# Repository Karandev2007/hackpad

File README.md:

# ASTRA DECK

## A cool macropad with 11 keys and a rotary encoder, a 128x32 OLED display and firmware using [KMK](https://github.com/KMKfw/kmk_firmware).

## Features:

- Privacy Shortcuts like Discord Mute/Unmute, Sleep, Lock, Desktop View, etc
- Media Control Keys like Mute, Play/Pause, Previous Track, Next Track.
- Media Control Keys with Rotary Encoder for Volume Control

---

## CAD

### Plate

### Base

### Case

## PCB and Schematic

---

## BOM

| Items                                |
| ------------------------------------ |
| 11x Cherry MX Switches               |
| 11x DSA Keycaps (Black)              |
| 1x EC11 Encoder Switch               |
| 1x SSD1306 128x32 0.91" OLED Display |
| 12x Through-hole 1N4148 Diodes       |
| 1x XIAO RP2040 Microcontroller       |
| 1x PCB                               |
| 1x Case                              |
| 1x Base (Printed, Black)             |
| 1x Plate (Printed, Orange)           |
| 4x M3x3.2mm SHCS Bolts               |

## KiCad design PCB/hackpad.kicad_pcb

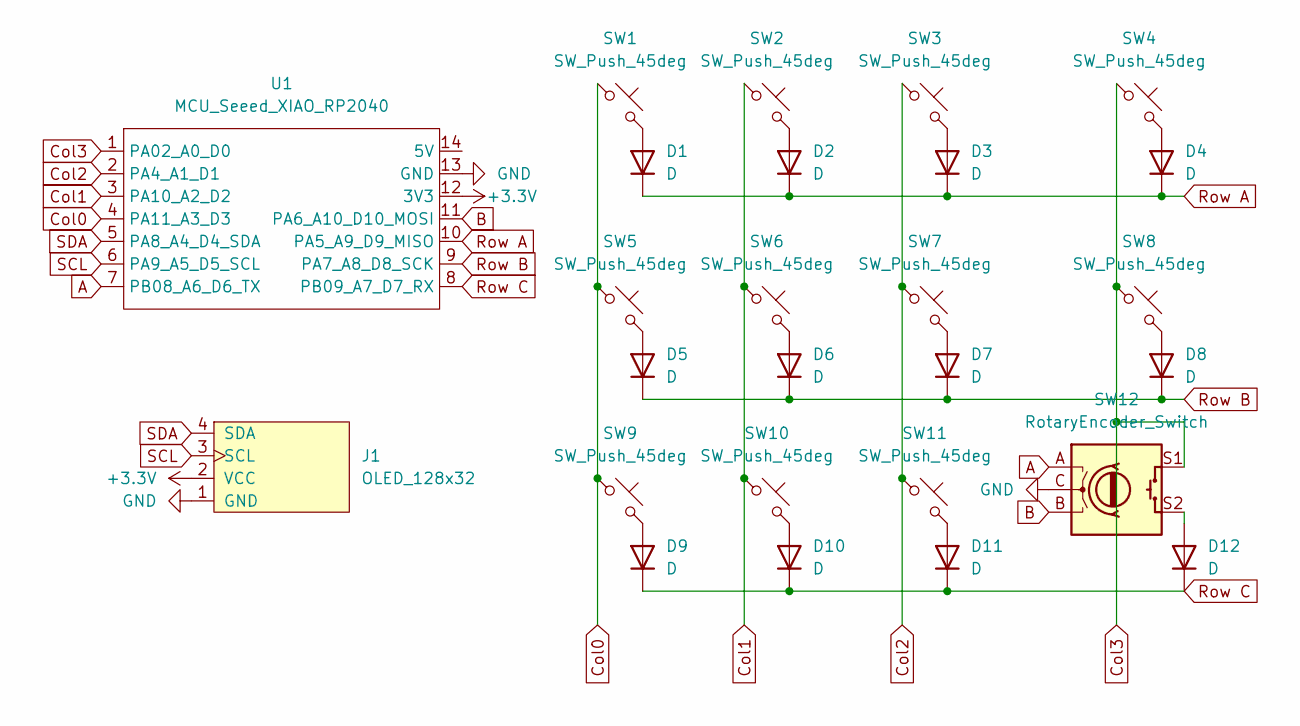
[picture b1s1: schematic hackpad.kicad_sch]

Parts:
D1, D2, D3, D4, D5, D6, D7, D8, D9, D10, D11, D12: D; Diode_DO-35
J1: OLED_128x32
SW1, SW2, SW3, SW4, SW5, SW6, SW7, SW8, SW9, SW10, SW11: SW_Push_45deg; MX_PCB_1.00u
SW12: RotaryEncoder_Switch; Encoder_EC11_MX
U1: MCU_Seeed_XIAO_RP2040; Seeed_XIAO_RP2040

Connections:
+3.3V: J1.2 (VCC), U1.12 (3V3)
A: SW12.A, U1.7 (PB08_A6_D6_TX)
B: SW12.B, U1.11 (PA6_A10_D10_MOSI)
Col0: SW1.1, SW5.1, SW9.1, U1.4 (PA11_A3_D3)
Col1: SW2.1, SW6.1, SW10.1, U1.3 (PA10_A2_D2)
Col2: SW3.1, SW7.1, SW11.1, U1.2 (PA4_A1_D1)
Col3: SW4.1, SW8.1, SW12.S1, U1.1 (PA02_A0_D0)
GND: J1.1 (GND), SW12.C, U1.13 (GND)
unnamed: D1.2 (A), SW1.2
unnamed: D2.2 (A), SW2.2
unnamed: D3.2 (A), SW3.2
unnamed: D4.2 (A), SW4.2
unnamed: D5.2 (A), SW5.2
unnamed: D6.2 (A), SW6.2
unnamed: D7.2 (A), SW7.2
unnamed: D8.2 (A), SW8.2
unnamed: D9.2 (A), SW9.2
unnamed: D10.2 (A), SW10.2
unnamed: D11.2 (A), SW11.2
unnamed: D12.2 (A), SW12.S2
Row A: D1.1 (K), D2.1 (K), D3.1 (K), D4.1 (K), U1.10 (PA5_A9_D9_MISO)
Row B: D5.1 (K), D6.1 (K), D7.1 (K), D8.1 (K), U1.9 (PA7_A8_D8_SCK)
Row C: D9.1 (K), D10.1 (K), D11.1 (K), D12.1 (K), U1.8 (PB09_A7_D7_RX)
SCL: J1.3 (SCL), U1.6 (PA9_A5_D5_SCL)
SDA: J1.4 (SDA), U1.5 (PA8_A4_D4_SDA)

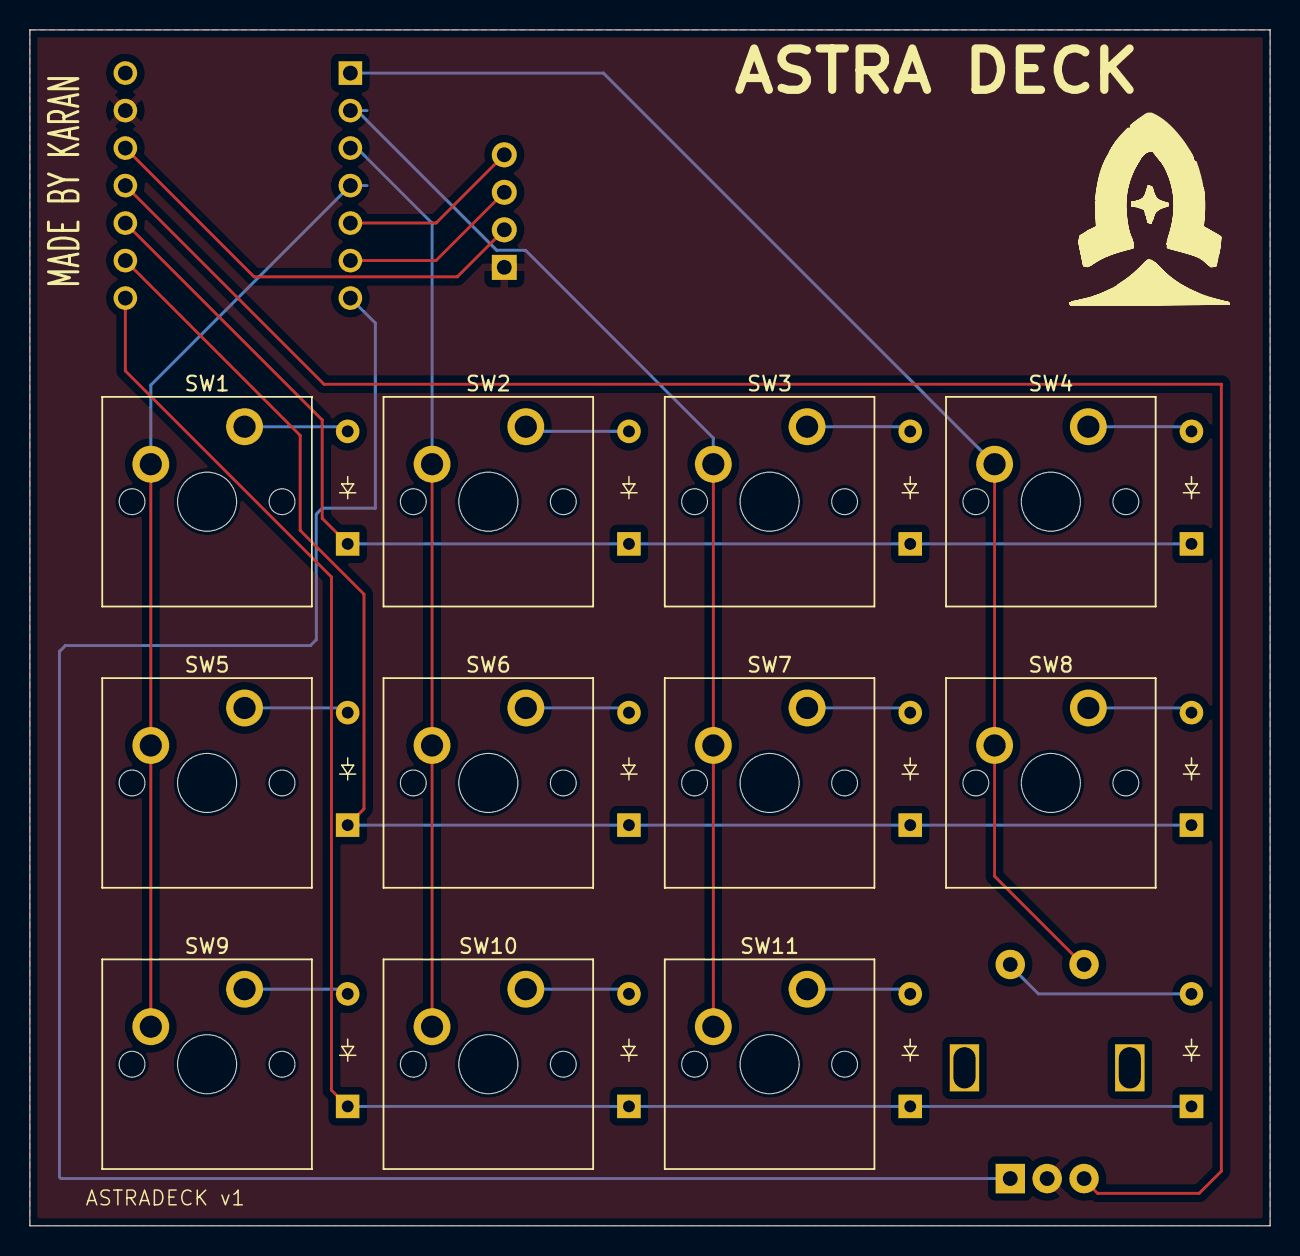
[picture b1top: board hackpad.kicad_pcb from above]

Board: 2 copper layers, 84.0 x 81.0 mm, 26 parts (1 on the bottom side), 25 nets.

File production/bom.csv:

Designator,Footprint,Quantity,Value,LCSC Part #
"D1, D10, D11, D12, D2, D3, D4, D5, D6, D7, D8, D9",Diode_DO-35,12,D,
J1,OLED_128x32,1,OLED_128x32,
"SW1, SW10, SW11, SW2, SW3, SW4, SW5, SW6, SW7, SW8, SW9",MX_PCB_1.00u,11,SW_Push_45deg,
SW12,Encoder_EC11_MX,1,RotaryEncoder_Switch,
U1,Seeed_XIAO_RP2040,1,MCU_Seeed_XIAO_RP2040,

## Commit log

2025-07-25 done
2025-08-02 fixes
2025-08-05 made edges smooth
    edges were sharp ;/
2025-08-15 fixes
    fixed heat issue on pcb
    made encoder slot bigger on CAD
    some file renames and duplications.
